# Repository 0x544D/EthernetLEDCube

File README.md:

# EthernetLEDCube
This project contains the PCB design files and software of the Ethernet controlled 6x6x6 LED Cube project. The project was successfully finished within the "System-on-Chip (SOC) + ARM Lab" course of TU Berlin.

Further information about the project can be found in the doc folder.

Project member:
* Tobias Minn
* Arne Salzwedel
* Julian Gog
* Max Thonagel

# Video of the result

# Pictures

Picture of the FPGA Board and the designed LED Cube PCB:

Animation on the Cube:

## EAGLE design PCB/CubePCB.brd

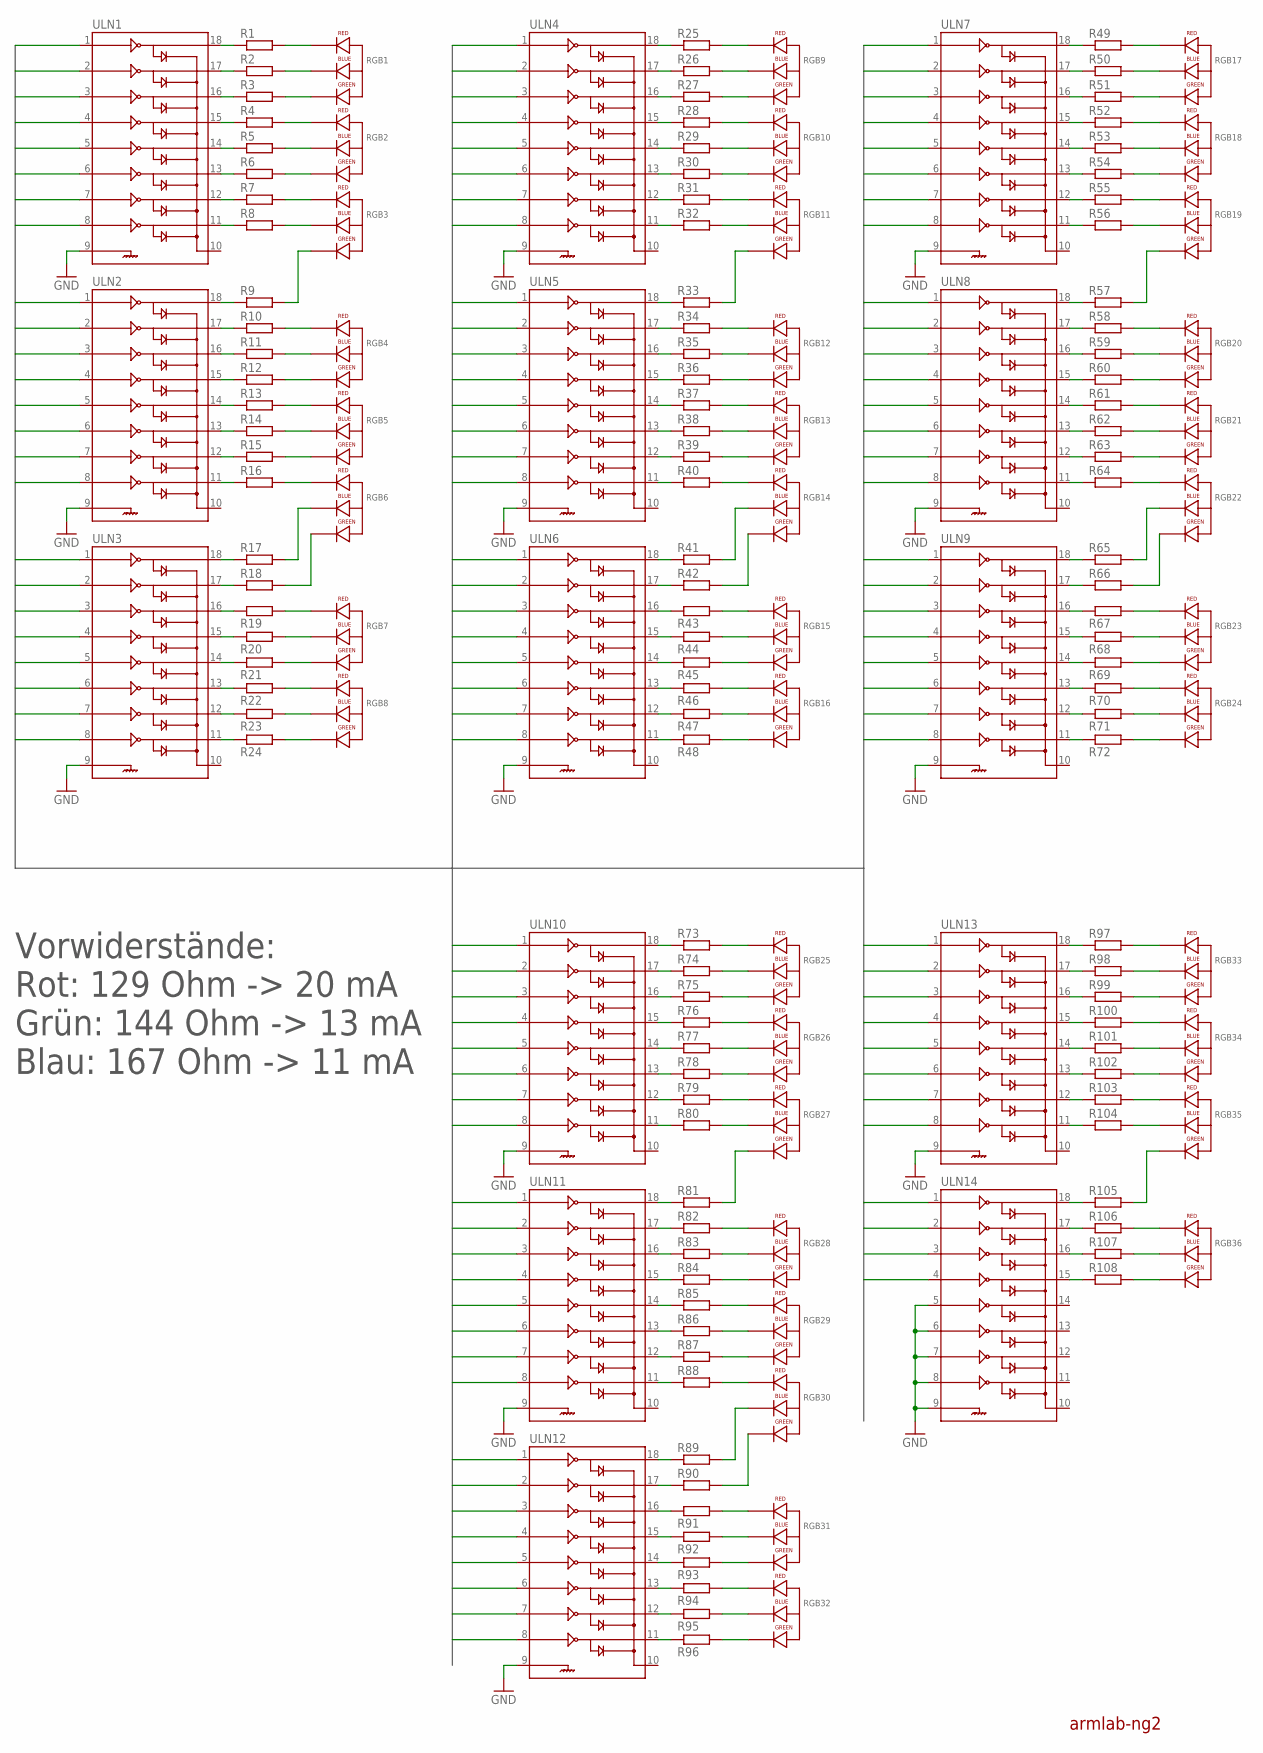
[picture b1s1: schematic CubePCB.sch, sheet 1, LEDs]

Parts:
R1, R2, R3, R4, R5, R6, R7, R8, R9, R10, R11, R12, R13, R14, R15, R16, R17, R18, R19, R20, R21, R22, R23, R24, R25, R26, R27, R28, R29, R30, R31, R32, R33, R34, R35, R36, R37, R38, R39, R40, R41, R42, R43, R44, R45, R46, R47, R48, R49, R50, R51, R52, R53, R54, R55, R56, R57, R58, R59, R60, R61, R62, R63, R64, R65, R66, R67, R68, R69, R70, R71, R72, R73, R74, R75, R76, R77, R78, R79, R80, R81, R82, R83, R84, R85, R86, R87, R88, R89, R90, R91, R92, R93, R94, R95, R96, R97, R98, R99, R100, R101, R102, R103, R104, R105, R106, R107, R108: R-EU_R0603; R0603
RGB1, RGB2, RGB3, RGB4, RGB5, RGB6, RGB7, RGB8, RGB9, RGB10, RGB11, RGB12, RGB13, RGB14, RGB15, RGB16, RGB17, RGB18, RGB19, RGB20, RGB21, RGB22, RGB23, RGB24, RGB25, RGB26, RGB27, RGB28, RGB29, RGB30, RGB31, RGB32, RGB33, RGB34, RGB35, RGB36: LED-RGB-CA-ANODE-SPLIT; LED-RGB-WO-ANODE
ULN1, ULN2, ULN3, ULN4, ULN5, ULN6, ULN7, ULN8, ULN9, ULN10, ULN11, ULN12, ULN13, ULN14: ULN2803SOICW; SO18L

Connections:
B1: ULN1.2; also elsewhere on the board
B2: ULN1.5; also elsewhere on the board
B3: ULN1.8; also elsewhere on the board
B4: ULN2.3; also elsewhere on the board
B5: ULN2.6; also elsewhere on the board
B6: ULN3.1; also elsewhere on the board
B7: ULN3.4; also elsewhere on the board
B8: ULN3.7; also elsewhere on the board
B9: ULN4.2; also elsewhere on the board
B10: ULN4.5; also elsewhere on the board
B11: ULN4.8; also elsewhere on the board
B12: ULN5.3; also elsewhere on the board
B13: ULN5.6; also elsewhere on the board
B14: ULN6.1; also elsewhere on the board
B15: ULN6.4; also elsewhere on the board
B16: ULN6.7; also elsewhere on the board
B17: ULN7.2; also elsewhere on the board
B18: ULN7.5; also elsewhere on the board
B19: ULN7.8; also elsewhere on the board
B20: ULN8.3; also elsewhere on the board
B21: ULN8.6; also elsewhere on the board
B22: ULN9.1; also elsewhere on the board
B23: ULN9.4; also elsewhere on the board
B24: ULN9.7; also elsewhere on the board
B25: ULN10.2; also elsewhere on the board
B26: ULN10.5; also elsewhere on the board
B27: ULN10.8; also elsewhere on the board
B28: ULN11.3; also elsewhere on the board
B29: ULN11.6; also elsewhere on the board
B30: ULN12.1; also elsewhere on the board
B31: ULN12.4; also elsewhere on the board
B32: ULN12.7; also elsewhere on the board
B33: ULN13.2; also elsewhere on the board
B34: ULN13.5; also elsewhere on the board
B35: ULN13.8; also elsewhere on the board
B36: ULN14.3; also elsewhere on the board
G1: ULN1.3; also elsewhere on the board
G2: ULN1.6; also elsewhere on the board
G3: ULN2.1; also elsewhere on the board
G4: ULN2.4; also elsewhere on the board
G5: ULN2.7; also elsewhere on the board
G6: ULN3.2; also elsewhere on the board
G7: ULN3.5; also elsewhere on the board
G8: ULN3.8; also elsewhere on the board
G9: ULN4.3; also elsewhere on the board
G10: ULN4.6; also elsewhere on the board
G11: ULN5.1; also elsewhere on the board
G12: ULN5.4; also elsewhere on the board
G13: ULN5.7; also elsewhere on the board
G14: ULN6.2; also elsewhere on the board
G15: ULN6.5; also elsewhere on the board
G16: ULN6.8; also elsewhere on the board
G17: ULN7.3; also elsewhere on the board
G18: ULN7.6; also elsewhere on the board
G19: ULN8.1; also elsewhere on the board
G20: ULN8.4; also elsewhere on the board
G21: ULN8.7; also elsewhere on the board
G22: ULN9.2; also elsewhere on the board
G23: ULN9.5; also elsewhere on the board
G24: ULN9.8; also elsewhere on the board
G25: ULN10.3; also elsewhere on the board
G26: ULN10.6; also elsewhere on the board
G27: ULN11.1; also elsewhere on the board
G28: ULN11.4; also elsewhere on the board
G29: ULN11.7; also elsewhere on the board
G30: ULN12.2; also elsewhere on the board
G31: ULN12.5; also elsewhere on the board
G32: ULN12.8; also elsewhere on the board
G33: ULN13.3; also elsewhere on the board
G34: ULN13.6; also elsewhere on the board
G35: ULN14.1; also elsewhere on the board
G36: ULN14.4; also elsewhere on the board
GND: ULN1.9, ULN2.9, ULN3.9, ULN4.9, ULN5.9, ULN6.9, ULN7.9, ULN8.9, ULN9.9, ULN10.9, ULN11.9, ULN12.9, ULN13.9, ULN14.5, ULN14.6, ULN14.7, ULN14.8, ULN14.9; also elsewhere on the board
unnamed: R1.1, ULN1.18
unnamed: R2.1, ULN1.17
unnamed: R3.1, ULN1.16
unnamed: R3.2, RGB1.G (GREEN_CATHODE)
unnamed: R2.2, RGB1.B (BLUE_CATHODE)
unnamed: R1.2, RGB1.R (RED_CATHODE)
unnamed: R4.1, ULN1.15
unnamed: R5.1, ULN1.14
unnamed: R6.1, ULN1.13
unnamed: R7.1, ULN1.12
unnamed: R6.2, RGB2.G (GREEN_CATHODE)
unnamed: R5.2, RGB2.B (BLUE_CATHODE)
unnamed: R4.2, RGB2.R (RED_CATHODE)
unnamed: R8.1, ULN1.11
unnamed: R19.1, ULN3.16
unnamed: R20.1, ULN3.15
unnamed: R9.2, RGB3.G (GREEN_CATHODE)
unnamed: R8.2, RGB3.B (BLUE_CATHODE)
unnamed: R7.2, RGB3.R (RED_CATHODE)
unnamed: R21.1, ULN3.14
unnamed: R22.1, ULN3.13
unnamed: R23.1, ULN3.12
unnamed: R12.2, RGB4.G (GREEN_CATHODE)
unnamed: R11.2, RGB4.B (BLUE_CATHODE)
unnamed: R10.2, RGB4.R (RED_CATHODE)
unnamed: R24.1, ULN3.11
unnamed: R27.2, RGB9.G (GREEN_CATHODE)
unnamed: R26.2, RGB9.B (BLUE_CATHODE)
unnamed: R15.2, RGB5.G (GREEN_CATHODE)
unnamed: R14.2, RGB5.B (BLUE_CATHODE)
unnamed: R13.2, RGB5.R (RED_CATHODE)
unnamed: R25.2, RGB9.R (RED_CATHODE)
unnamed: R30.2, RGB10.G (GREEN_CATHODE)
unnamed: R29.2, RGB10.B (BLUE_CATHODE)
unnamed: R18.2, RGB6.G (GREEN_CATHODE)
unnamed: R17.2, RGB6.B (BLUE_CATHODE)
unnamed: R16.2, RGB6.R (RED_CATHODE)
unnamed: R28.2, RGB10.R (RED_CATHODE)
unnamed: R33.2, RGB11.G (GREEN_CATHODE)
unnamed: R32.2, RGB11.B (BLUE_CATHODE)
unnamed: R31.2, RGB11.R (RED_CATHODE)
unnamed: R36.2, RGB12.G (GREEN_CATHODE)
unnamed: R35.2, RGB12.B (BLUE_CATHODE)
unnamed: R34.2, RGB12.R (RED_CATHODE)
unnamed: R19.2, RGB7.R (RED_CATHODE)
unnamed: R20.2, RGB7.B (BLUE_CATHODE)
unnamed: R21.2, RGB7.G (GREEN_CATHODE)
unnamed: R22.2, RGB8.R (RED_CATHODE)
unnamed: R23.2, RGB8.B (BLUE_CATHODE)
unnamed: R24.2, RGB8.G (GREEN_CATHODE)
unnamed: R39.2, RGB13.G (GREEN_CATHODE)
unnamed: R38.2, RGB13.B (BLUE_CATHODE)
unnamed: R9.1, ULN2.18
unnamed: R10.1, ULN2.17
unnamed: R11.1, ULN2.16
unnamed: R12.1, ULN2.15
unnamed: R13.1, ULN2.14
unnamed: R14.1, ULN2.13
unnamed: R15.1, ULN2.12
unnamed: R16.1, ULN2.11
unnamed: R17.1, ULN3.18
unnamed: R18.1, ULN3.17
unnamed: R37.2, RGB13.R (RED_CATHODE)
unnamed: R42.2, RGB14.G (GREEN_CATHODE)
unnamed: R41.2, RGB14.B (BLUE_CATHODE)
unnamed: R40.2, RGB14.R (RED_CATHODE)
unnamed: R25.1, ULN4.18
unnamed: R26.1, ULN4.17
unnamed: R27.1, ULN4.16
unnamed: R28.1, ULN4.15
unnamed: R29.1, ULN4.14
unnamed: R30.1, ULN4.13
unnamed: R31.1, ULN4.12
unnamed: R32.1, ULN4.11
unnamed: R33.1, ULN5.18
unnamed: R34.1, ULN5.17
unnamed: R35.1, ULN5.16
unnamed: R36.1, ULN5.15
unnamed: R37.1, ULN5.14
unnamed: R38.1, ULN5.13
unnamed: R39.1, ULN5.12
unnamed: R40.1, ULN5.11
unnamed: R41.1, ULN6.18
unnamed: R42.1, ULN6.17
unnamed: R43.1, ULN6.16
unnamed: R44.1, ULN6.15
unnamed: R45.1, ULN6.14
unnamed: R46.1, ULN6.13
unnamed: R47.1, ULN6.12
unnamed: R48.1, ULN6.11
unnamed: R43.2, RGB15.R (RED_CATHODE)
unnamed: R44.2, RGB15.B (BLUE_CATHODE)
unnamed: R45.2, RGB15.G (GREEN_CATHODE)
unnamed: R46.2, RGB16.R (RED_CATHODE)
unnamed: R47.2, RGB16.B (BLUE_CATHODE)
unnamed: R48.2, RGB16.G (GREEN_CATHODE)
unnamed: R51.2, RGB17.G (GREEN_CATHODE)
unnamed: R50.2, RGB17.B (BLUE_CATHODE)
unnamed: R49.2, RGB17.R (RED_CATHODE)
unnamed: R54.2, RGB18.G (GREEN_CATHODE)
unnamed: R53.2, RGB18.B (BLUE_CATHODE)
unnamed: R52.2, RGB18.R (RED_CATHODE)
unnamed: R57.2, RGB19.G (GREEN_CATHODE)
unnamed: R56.2, RGB19.B (BLUE_CATHODE)
unnamed: R55.2, RGB19.R (RED_CATHODE)
unnamed: R60.2, RGB20.G (GREEN_CATHODE)
unnamed: R59.2, RGB20.B (BLUE_CATHODE)
unnamed: R58.2, RGB20.R (RED_CATHODE)
unnamed: R63.2, RGB21.G (GREEN_CATHODE)
unnamed: R62.2, RGB21.B (BLUE_CATHODE)
unnamed: R61.2, RGB21.R (RED_CATHODE)
unnamed: R66.2, RGB22.G (GREEN_CATHODE)
unnamed: R65.2, RGB22.B (BLUE_CATHODE)
unnamed: R64.2, RGB22.R (RED_CATHODE)
unnamed: R49.1, ULN7.18
unnamed: R50.1, ULN7.17
unnamed: R51.1, ULN7.16
unnamed: R52.1, ULN7.15
unnamed: R53.1, ULN7.14
unnamed: R54.1, ULN7.13
unnamed: R55.1, ULN7.12
unnamed: R56.1, ULN7.11
unnamed: R57.1, ULN8.18
unnamed: R58.1, ULN8.17
unnamed: R59.1, ULN8.16
unnamed: R60.1, ULN8.15
unnamed: R61.1, ULN8.14
unnamed: R62.1, ULN8.13
unnamed: R63.1, ULN8.12
unnamed: R64.1, ULN8.11
unnamed: R65.1, ULN9.18
unnamed: R66.1, ULN9.17
unnamed: R67.1, ULN9.16
unnamed: R68.1, ULN9.15
unnamed: R69.1, ULN9.14
unnamed: R70.1, ULN9.13
unnamed: R71.1, ULN9.12
unnamed: R72.1, ULN9.11
unnamed: R67.2, RGB23.R (RED_CATHODE)
unnamed: R68.2, RGB23.B (BLUE_CATHODE)
unnamed: R69.2, RGB23.G (GREEN_CATHODE)
unnamed: R70.2, RGB24.R (RED_CATHODE)
unnamed: R71.2, RGB24.B (BLUE_CATHODE)
unnamed: R72.2, RGB24.G (GREEN_CATHODE)
unnamed: R75.2, RGB25.G (GREEN_CATHODE)
unnamed: R74.2, RGB25.B (BLUE_CATHODE)
unnamed: R73.2, RGB25.R (RED_CATHODE)
unnamed: R78.2, RGB26.G (GREEN_CATHODE)
unnamed: R77.2, RGB26.B (BLUE_CATHODE)
unnamed: R76.2, RGB26.R (RED_CATHODE)
unnamed: R81.2, RGB27.G (GREEN_CATHODE)
unnamed: R80.2, RGB27.B (BLUE_CATHODE)
unnamed: R79.2, RGB27.R (RED_CATHODE)
unnamed: R84.2, RGB28.G (GREEN_CATHODE)
unnamed: R83.2, RGB28.B (BLUE_CATHODE)
unnamed: R82.2, RGB28.R (RED_CATHODE)
unnamed: R87.2, RGB29.G (GREEN_CATHODE)
unnamed: R86.2, RGB29.B (BLUE_CATHODE)
unnamed: R85.2, RGB29.R (RED_CATHODE)
unnamed: R90.2, RGB30.G (GREEN_CATHODE)
unnamed: R89.2, RGB30.B (BLUE_CATHODE)
unnamed: R88.2, RGB30.R (RED_CATHODE)
unnamed: R73.1, ULN10.18
unnamed: R74.1, ULN10.17
unnamed: R75.1, ULN10.16
unnamed: R76.1, ULN10.15
unnamed: R77.1, ULN10.14
unnamed: R78.1, ULN10.13
unnamed: R79.1, ULN10.12
unnamed: R80.1, ULN10.11
unnamed: R81.1, ULN11.18
unnamed: R82.1, ULN11.17
unnamed: R83.1, ULN11.16
unnamed: R84.1, ULN11.15
unnamed: R85.1, ULN11.14
unnamed: R86.1, ULN11.13
unnamed: R87.1, ULN11.12
unnamed: R88.1, ULN11.11
unnamed: R89.1, ULN12.18
unnamed: R90.1, ULN12.17
unnamed: R91.1, ULN12.16
unnamed: R92.1, ULN12.15
unnamed: R93.1, ULN12.14
unnamed: R94.1, ULN12.13
unnamed: R95.1, ULN12.12
unnamed: R96.1, ULN12.11
unnamed: R91.2, RGB31.R (RED_CATHODE)
unnamed: R92.2, RGB31.B (BLUE_CATHODE)
unnamed: R93.2, RGB31.G (GREEN_CATHODE)
unnamed: R94.2, RGB32.R (RED_CATHODE)
unnamed: R95.2, RGB32.B (BLUE_CATHODE)
unnamed: R96.2, RGB32.G (GREEN_CATHODE)
unnamed: R99.2, RGB33.G (GREEN_CATHODE)
unnamed: R98.2, RGB33.B (BLUE_CATHODE)
unnamed: R97.2, RGB33.R (RED_CATHODE)
unnamed: R102.2, RGB34.G (GREEN_CATHODE)
unnamed: R101.2, RGB34.B (BLUE_CATHODE)
unnamed: R100.2, RGB34.R (RED_CATHODE)
unnamed: R105.2, RGB35.G (GREEN_CATHODE)
unnamed: R104.2, RGB35.B (BLUE_CATHODE)
unnamed: R103.2, RGB35.R (RED_CATHODE)
unnamed: R108.2, RGB36.G (GREEN_CATHODE)
unnamed: R107.2, RGB36.B (BLUE_CATHODE)
unnamed: R106.2, RGB36.R (RED_CATHODE)
unnamed: R97.1, ULN13.18
unnamed: R98.1, ULN13.17
unnamed: R99.1, ULN13.16
unnamed: R100.1, ULN13.15
unnamed: R101.1, ULN13.14
unnamed: R102.1, ULN13.13
unnamed: R103.1, ULN13.12
unnamed: R104.1, ULN13.11
unnamed: R105.1, ULN14.18
unnamed: R106.1, ULN14.17
unnamed: R107.1, ULN14.16
unnamed: R108.1, ULN14.15
R1: ULN1.1; also elsewhere on the board
R2: ULN1.4; also elsewhere on the board
R3: ULN1.7; also elsewhere on the board
R4: ULN2.2; also elsewhere on the board
R5: ULN2.5; also elsewhere on the board
R6: ULN2.8; also elsewhere on the board
R7: ULN3.3; also elsewhere on the board
R8: ULN3.6; also elsewhere on the board
R9: ULN4.1; also elsewhere on the board
R10: ULN4.4; also elsewhere on the board
R11: ULN4.7; also elsewhere on the board
R12: ULN5.2; also elsewhere on the board
R13: ULN5.5; also elsewhere on the board
R14: ULN5.8; also elsewhere on the board
R15: ULN6.3; also elsewhere on the board
R16: ULN6.6; also elsewhere on the board
R17: ULN7.1; also elsewhere on the board
R18: ULN7.4; also elsewhere on the board
R19: ULN7.7; also elsewhere on the board
R20: ULN8.2; also elsewhere on the board
R21: ULN8.5; also elsewhere on the board
R22: ULN8.8; also elsewhere on the board
R23: ULN9.3; also elsewhere on the board
R24: ULN9.6; also elsewhere on the board
R25: ULN10.1; also elsewhere on the board
R26: ULN10.4; also elsewhere on the board
R27: ULN10.7; also elsewhere on the board
R28: ULN11.2; also elsewhere on the board
R29: ULN11.5; also elsewhere on the board
R30: ULN11.8; also elsewhere on the board
R31: ULN12.3; also elsewhere on the board
R32: ULN12.6; also elsewhere on the board
R33: ULN13.1; also elsewhere on the board
R34: ULN13.4; also elsewhere on the board
R35: ULN13.7; also elsewhere on the board
R36: ULN14.2; also elsewhere on the board

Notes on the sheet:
Vorwiderstände: Rot: 129 Ohm -> 20 mA Grün: 144 Ohm -> 13 mA Blau: 167 Ohm -> 11 mA
armlab-ng2

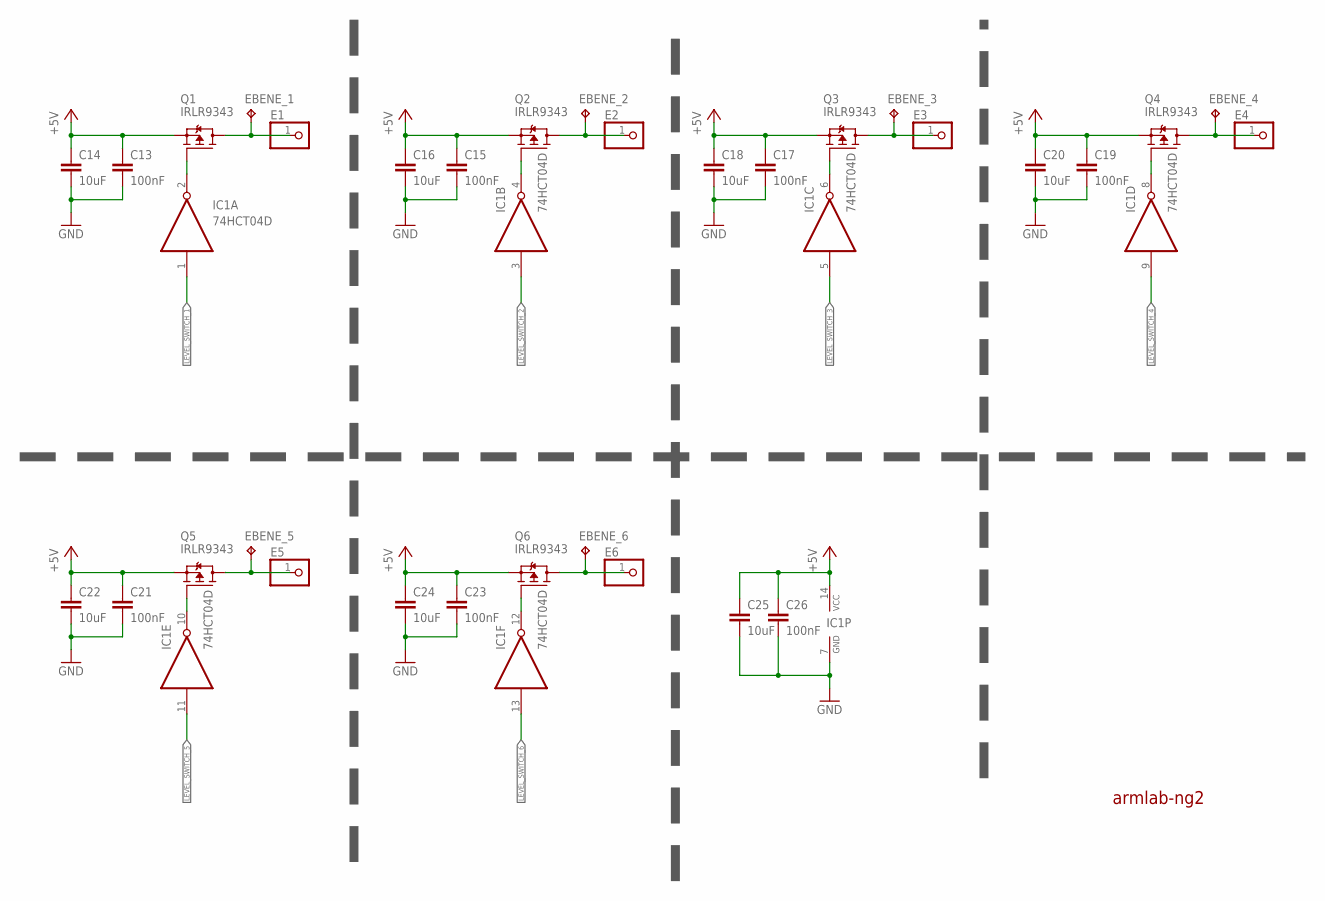
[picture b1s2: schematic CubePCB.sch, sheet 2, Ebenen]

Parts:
C13, C15, C17, C19, C21, C23, C26: 100nF; C0603K
C14, C16, C18, C20, C22, C24, C25: 10uF; C0603K
E1, E2, E3, E4, E5, E6: PINHD-1X1/LONG; 1X01
EBENE_1, EBENE_2, EBENE_3, EBENE_4, EBENE_5, EBENE_6: TPB1,27; B1,27
IC1: 74HCT04D; SO14
Q1, Q2, Q3, Q4, Q5, Q6: IRLR9343; TO252

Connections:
+5V: C13.1, C14.1, C15.1, C16.1, C17.1, C18.1, C19.1, C20.1, C21.1, C22.1, C23.1, C24.1, C25.1, C26.1, IC1.14 (VCC), Q1.2 (S), Q2.2 (S), Q3.2 (S), Q4.2 (S), Q5.2 (S), Q6.2 (S); also elsewhere on the board
EBENE_1: E1.1, EBENE_1.TP, Q1.3 (D)
EBENE_2: E2.1, EBENE_2.TP, Q2.3 (D)
EBENE_3: E3.1, EBENE_3.TP, Q3.3 (D)
EBENE_4: E4.1, EBENE_4.TP, Q4.3 (D)
EBENE_5: E5.1, EBENE_5.TP, Q5.3 (D)
EBENE_6: E6.1, EBENE_6.TP, Q6.3 (D)
GND: C13.2, C14.2, C15.2, C16.2, C17.2, C18.2, C19.2, C20.2, C21.2, C22.2, C23.2, C24.2, C25.2, C26.2, IC1.7 (GND); also elsewhere on the board
LEVEL_SWITCH_1: IC1.1 (I); also elsewhere on the board
LEVEL_SWITCH_2: IC1.3 (I); also elsewhere on the board
LEVEL_SWITCH_3: IC1.5 (I); also elsewhere on the board
LEVEL_SWITCH_4: IC1.9 (I); also elsewhere on the board
LEVEL_SWITCH_5: IC1.11 (I); also elsewhere on the board
LEVEL_SWITCH_6: IC1.13 (I); also elsewhere on the board
unnamed: IC1.4 (O), Q2.1 (G)
unnamed: IC1.2 (O), Q1.1 (G)
unnamed: IC1.6 (O), Q3.1 (G)
unnamed: IC1.8 (O), Q4.1 (G)
unnamed: IC1.10 (O), Q5.1 (G)
unnamed: IC1.12 (O), Q6.1 (G)

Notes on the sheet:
armlab-ng2

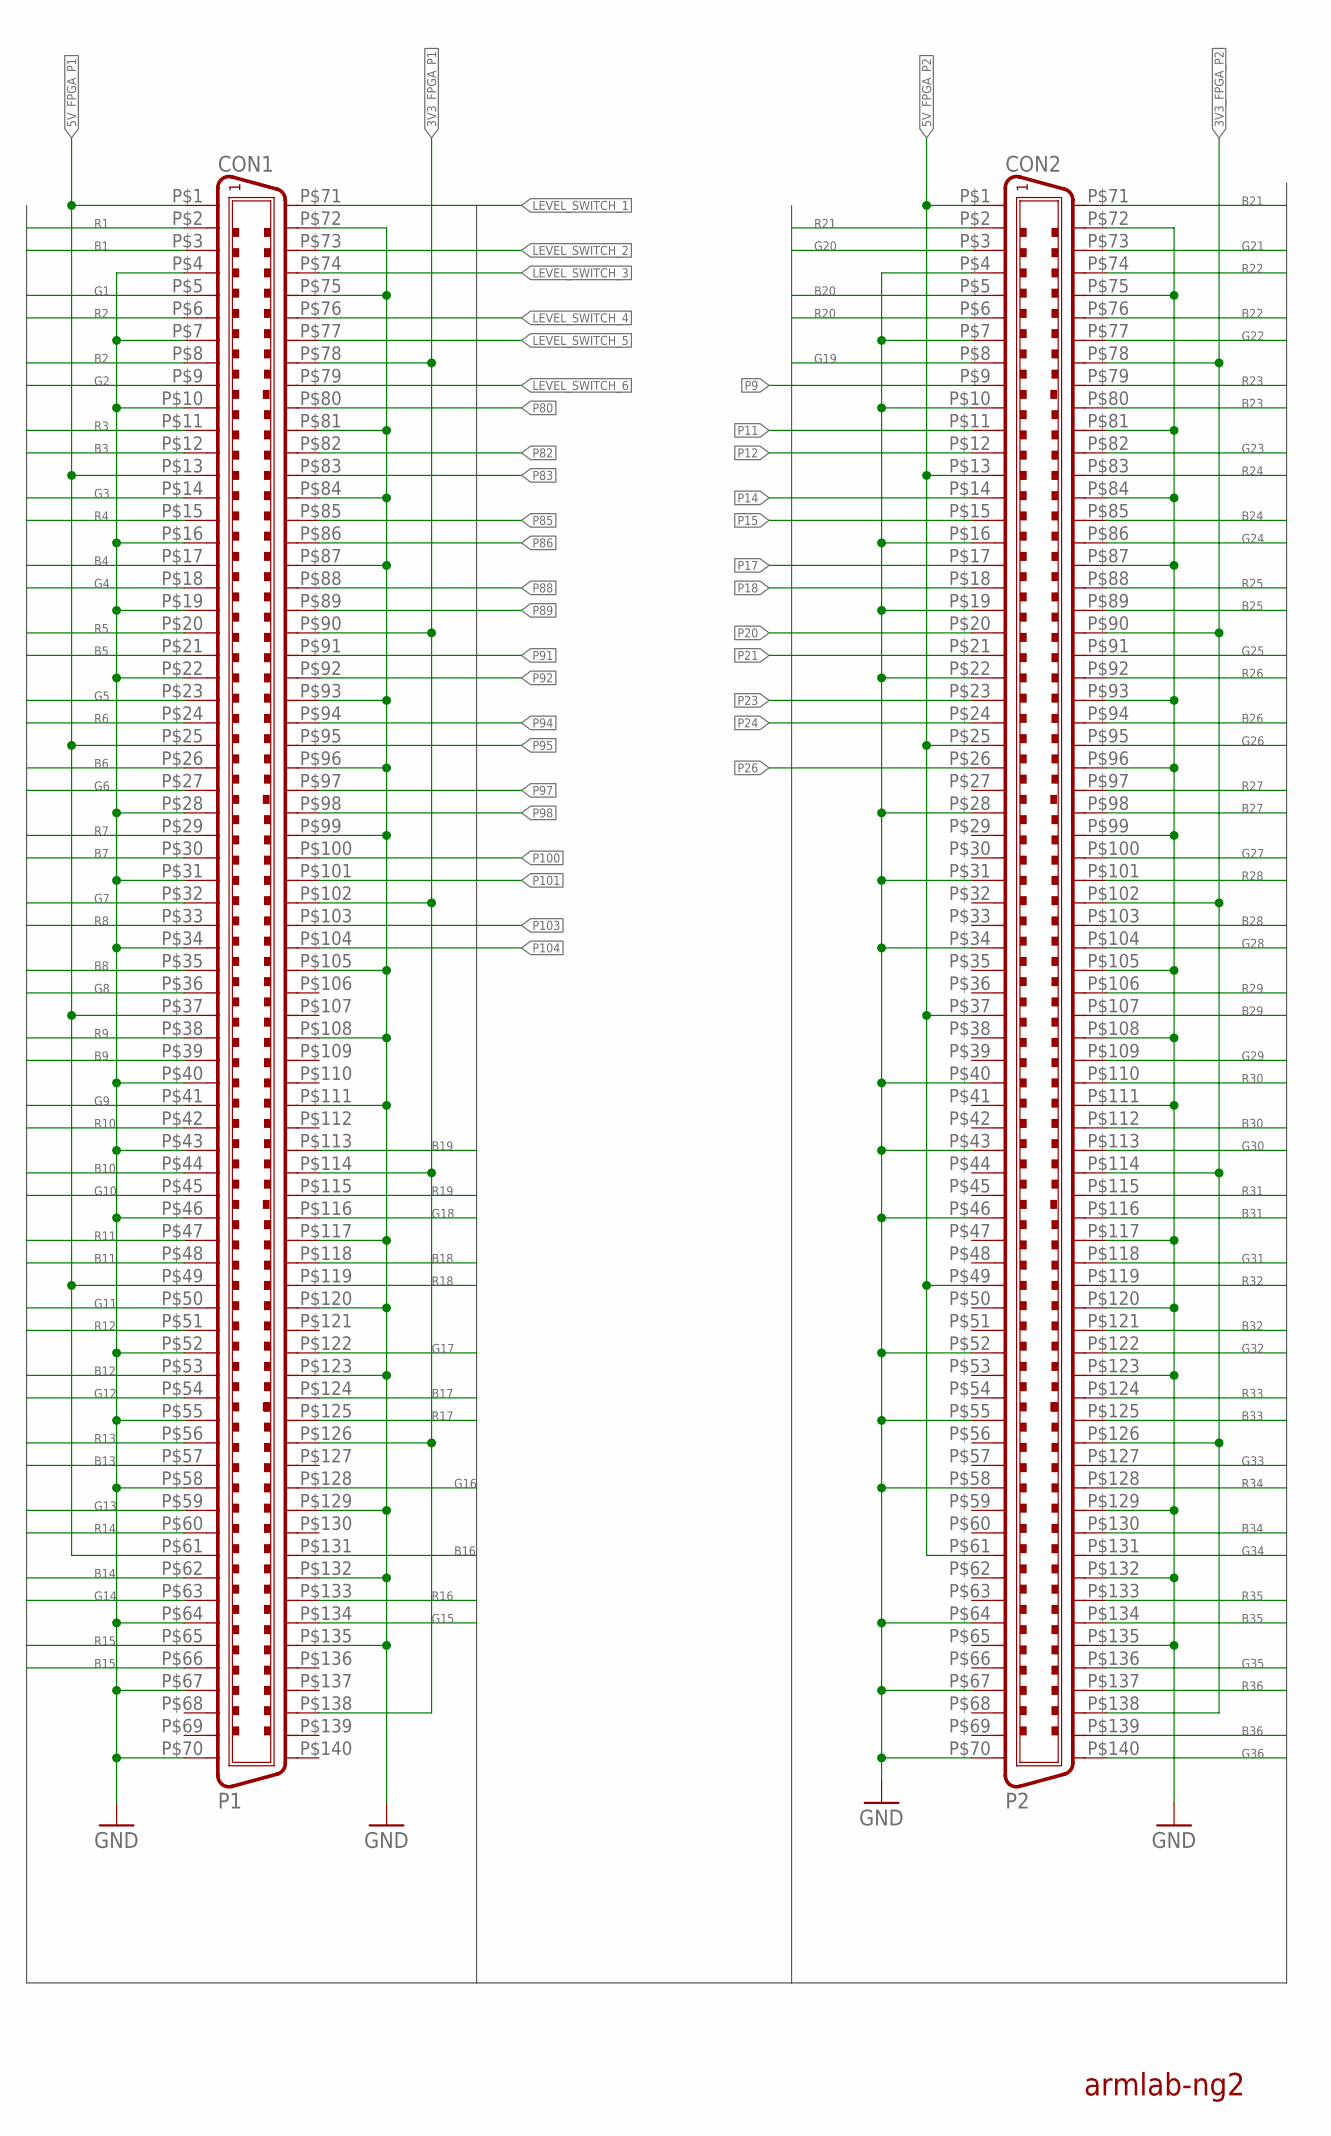
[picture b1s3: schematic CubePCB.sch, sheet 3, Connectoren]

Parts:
CON1: P1; 140-FH0.8
CON2: P2; 140-FH0.8

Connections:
3V3_FPGA_P1: CON1.P$78 (78), CON1.P$90 (90), CON1.P$102 (102), CON1.P$114 (114), CON1.P$126 (126), CON1.P$138 (138)
3V3_FPGA_P2: CON2.P$78 (78), CON2.P$90 (90), CON2.P$102 (102), CON2.P$114 (114), CON2.P$126 (126), CON2.P$138 (138)
5V_FPGA_P1: CON1.P$1 (1), CON1.P$13 (13), CON1.P$25 (25), CON1.P$37 (37), CON1.P$49 (49), CON1.P$61 (61)
5V_FPGA_P2: CON2.P$1 (1), CON2.P$13 (13), CON2.P$25 (25), CON2.P$37 (37), CON2.P$49 (49), CON2.P$61 (61)
B1: CON1.P$3 (3); also elsewhere on the board
B2: CON1.P$8 (8); also elsewhere on the board
B3: CON1.P$12 (12); also elsewhere on the board
B4: CON1.P$17 (17); also elsewhere on the board
B5: CON1.P$21 (21); also elsewhere on the board
B6: CON1.P$26 (26); also elsewhere on the board
B7: CON1.P$30 (30); also elsewhere on the board
B8: CON1.P$35 (35); also elsewhere on the board
B9: CON1.P$39 (39); also elsewhere on the board
B10: CON1.P$44 (44); also elsewhere on the board
B11: CON1.P$48 (48); also elsewhere on the board
B12: CON1.P$53 (53); also elsewhere on the board
B13: CON1.P$57 (57); also elsewhere on the board
B14: CON1.P$62 (62); also elsewhere on the board
B15: CON1.P$66 (66); also elsewhere on the board
B16: CON1.P$131 (131); also elsewhere on the board
B17: CON1.P$124 (124); also elsewhere on the board
B18: CON1.P$118 (118); also elsewhere on the board
B19: CON1.P$113 (113); also elsewhere on the board
B20: CON2.P$5 (5); also elsewhere on the board
B21: CON2.P$71 (71); also elsewhere on the board
B22: CON2.P$76 (76); also elsewhere on the board
B23: CON2.P$80 (80); also elsewhere on the board
B24: CON2.P$85 (85); also elsewhere on the board
B25: CON2.P$89 (89); also elsewhere on the board
B26: CON2.P$94 (94); also elsewhere on the board
B27: CON2.P$98 (98); also elsewhere on the board
B28: CON2.P$103 (103); also elsewhere on the board
B29: CON2.P$107 (107); also elsewhere on the board
B30: CON2.P$112 (112); also elsewhere on the board
B31: CON2.P$116 (116); also elsewhere on the board
B32: CON2.P$121 (121); also elsewhere on the board
B33: CON2.P$125 (125); also elsewhere on the board
B34: CON2.P$130 (130); also elsewhere on the board
B35: CON2.P$134 (134); also elsewhere on the board
B36: CON2.P$139 (139); also elsewhere on the board
G1: CON1.P$5 (5); also elsewhere on the board
G2: CON1.P$9 (9); also elsewhere on the board
G3: CON1.P$14 (14); also elsewhere on the board
G4: CON1.P$18 (18); also elsewhere on the board
G5: CON1.P$23 (23); also elsewhere on the board
G6: CON1.P$27 (27); also elsewhere on the board
G7: CON1.P$32 (32); also elsewhere on the board
G8: CON1.P$36 (36); also elsewhere on the board
G9: CON1.P$41 (41); also elsewhere on the board
G10: CON1.P$45 (45); also elsewhere on the board
G11: CON1.P$50 (50); also elsewhere on the board
G12: CON1.P$54 (54); also elsewhere on the board
G13: CON1.P$59 (59); also elsewhere on the board
G14: CON1.P$63 (63); also elsewhere on the board
G15: CON1.P$134 (134); also elsewhere on the board
G16: CON1.P$128 (128); also elsewhere on the board
G17: CON1.P$122 (122); also elsewhere on the board
G18: CON1.P$116 (116); also elsewhere on the board
G19: CON2.P$8 (8); also elsewhere on the board
G20: CON2.P$3 (3); also elsewhere on the board
G21: CON2.P$73 (73); also elsewhere on the board
G22: CON2.P$77 (77); also elsewhere on the board
G23: CON2.P$82 (82); also elsewhere on the board
G24: CON2.P$86 (86); also elsewhere on the board
G25: CON2.P$91 (91); also elsewhere on the board
G26: CON2.P$95 (95); also elsewhere on the board
G27: CON2.P$100 (100); also elsewhere on the board
G28: CON2.P$104 (104); also elsewhere on the board
G29: CON2.P$109 (109); also elsewhere on the board
G30: CON2.P$113 (113); also elsewhere on the board
G31: CON2.P$118 (118); also elsewhere on the board
G32: CON2.P$122 (122); also elsewhere on the board
G33: CON2.P$127 (127); also elsewhere on the board
G34: CON2.P$131 (131); also elsewhere on the board
G35: CON2.P$136 (136); also elsewhere on the board
G36: CON2.P$140 (140); also elsewhere on the board
GND: CON1.P$4 (4), CON1.P$7 (7), CON1.P$10 (10), CON1.P$16 (16), CON1.P$19 (19), CON1.P$22 (22), CON1.P$28 (28), CON1.P$31 (31), CON1.P$34 (34), CON1.P$40 (40), CON1.P$43 (43), CON1.P$46 (46), CON1.P$52 (52), CON1.P$55 (55), CON1.P$58 (58), CON1.P$64 (64), CON1.P$67 (67), CON1.P$70 (70), CON1.P$72 (72), CON1.P$75 (75), CON1.P$81 (81), CON1.P$84 (84), CON1.P$87 (87), CON1.P$93 (93), CON1.P$96 (96), CON1.P$99 (99), CON1.P$105 (105), CON1.P$108 (108), CON1.P$111 (111), CON1.P$117 (117), CON1.P$120 (120), CON1.P$123 (123), CON1.P$129 (129), CON1.P$132 (132), CON1.P$135 (135), CON2.P$4 (4), CON2.P$7 (7), CON2.P$10 (10), CON2.P$16 (16), CON2.P$19 (19), CON2.P$22 (22), CON2.P$28 (28), CON2.P$31 (31), CON2.P$34 (34), CON2.P$40 (40), CON2.P$43 (43), CON2.P$46 (46), CON2.P$52 (52), CON2.P$55 (55), CON2.P$58 (58), CON2.P$64 (64), CON2.P$67 (67), CON2.P$70 (70), CON2.P$72 (72), CON2.P$75 (75), CON2.P$81 (81), CON2.P$84 (84), CON2.P$87 (87), CON2.P$93 (93), CON2.P$96 (96), CON2.P$99 (99), CON2.P$105 (105), CON2.P$108 (108), CON2.P$111 (111), CON2.P$117 (117), CON2.P$120 (120), CON2.P$123 (123), CON2.P$129 (129), CON2.P$132 (132), CON2.P$135 (135); also elsewhere on the board
LEVEL_SWITCH_1: CON1.P$71 (71); also elsewhere on the board
LEVEL_SWITCH_2: CON1.P$73 (73); also elsewhere on the board
LEVEL_SWITCH_3: CON1.P$74 (74); also elsewhere on the board
LEVEL_SWITCH_4: CON1.P$76 (76); also elsewhere on the board
LEVEL_SWITCH_5: CON1.P$77 (77); also elsewhere on the board
LEVEL_SWITCH_6: CON1.P$79 (79); also elsewhere on the board
P9: CON2.P$9 (9)
P11: CON2.P$11 (11)
P12: CON2.P$12 (12)
P14: CON2.P$14 (14)
P15: CON2.P$15 (15)
P17: CON2.P$17 (17)
P18: CON2.P$18 (18)
P20: CON2.P$20 (20)
P21: CON2.P$21 (21)
P23: CON2.P$23 (23)
P24: CON2.P$24 (24)
P26: CON2.P$26 (26)
P80: CON1.P$80 (80)
P82: CON1.P$82 (82)
P83: CON1.P$83 (83)
P85: CON1.P$85 (85)
P86: CON1.P$86 (86)
P88: CON1.P$88 (88)
P89: CON1.P$89 (89)
P91: CON1.P$91 (91)
P92: CON1.P$92 (92)
P94: CON1.P$94 (94)
P95: CON1.P$95 (95)
P97: CON1.P$97 (97)
P98: CON1.P$98 (98)
P100: CON1.P$100 (100)
P101: CON1.P$101 (101)
P103: CON1.P$103 (103)
P104: CON1.P$104 (104)
R1: CON1.P$2 (2); also elsewhere on the board
R2: CON1.P$6 (6); also elsewhere on the board
R3: CON1.P$11 (11); also elsewhere on the board
R4: CON1.P$15 (15); also elsewhere on the board
R5: CON1.P$20 (20); also elsewhere on the board
R6: CON1.P$24 (24); also elsewhere on the board
R7: CON1.P$29 (29); also elsewhere on the board
R8: CON1.P$33 (33); also elsewhere on the board
R9: CON1.P$38 (38); also elsewhere on the board
R10: CON1.P$42 (42); also elsewhere on the board
R11: CON1.P$47 (47); also elsewhere on the board
R12: CON1.P$51 (51); also elsewhere on the board
R13: CON1.P$56 (56); also elsewhere on the board
R14: CON1.P$60 (60); also elsewhere on the board
R15: CON1.P$65 (65); also elsewhere on the board
R16: CON1.P$133 (133); also elsewhere on the board
R17: CON1.P$125 (125); also elsewhere on the board
R18: CON1.P$119 (119); also elsewhere on the board
R19: CON1.P$115 (115); also elsewhere on the board
R20: CON2.P$6 (6); also elsewhere on the board
R21: CON2.P$2 (2); also elsewhere on the board
R22: CON2.P$74 (74); also elsewhere on the board
R23: CON2.P$79 (79); also elsewhere on the board
R24: CON2.P$83 (83); also elsewhere on the board
R25: CON2.P$88 (88); also elsewhere on the board
R26: CON2.P$92 (92); also elsewhere on the board
R27: CON2.P$97 (97); also elsewhere on the board
R28: CON2.P$101 (101); also elsewhere on the board
R29: CON2.P$106 (106); also elsewhere on the board
R30: CON2.P$110 (110); also elsewhere on the board
R31: CON2.P$115 (115); also elsewhere on the board
R32: CON2.P$119 (119); also elsewhere on the board
R33: CON2.P$124 (124); also elsewhere on the board
R34: CON2.P$128 (128); also elsewhere on the board
R35: CON2.P$133 (133); also elsewhere on the board
R36: CON2.P$137 (137); also elsewhere on the board

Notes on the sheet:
armlab-ng2

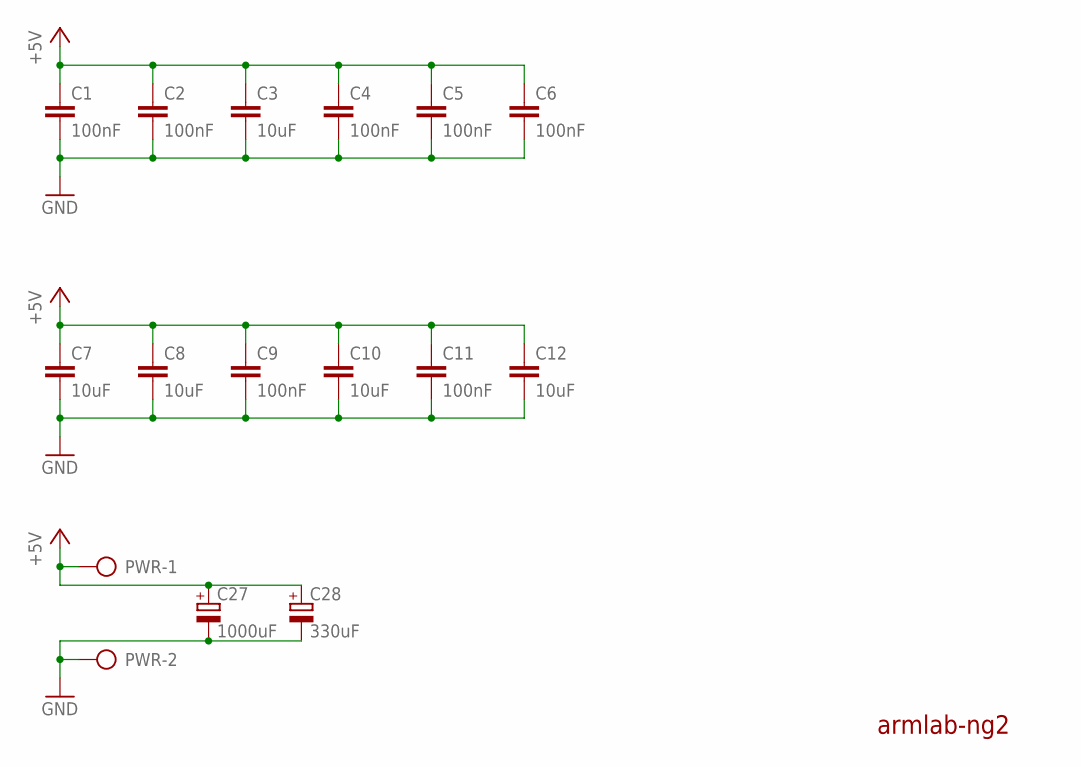
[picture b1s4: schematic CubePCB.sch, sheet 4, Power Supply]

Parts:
C1, C2, C4, C5, C6, C9, C11: 100nF; C0603K
C3, C7, C8, C10, C12: 10uF; C0603K
C27: 1000uF; E5-10,5
C28: 330uF; E3,5-8
PWR: AK500/2

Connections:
+5V: C1.1, C2.1, C3.1, C4.1, C5.1, C6.1, C7.1, C8.1, C9.1, C10.1, C11.1, C12.1, C27.+, C28.+, PWR.1; also elsewhere on the board
GND: C1.2, C2.2, C3.2, C4.2, C5.2, C6.2, C7.2, C8.2, C9.2, C10.2, C11.2, C12.2, C27.-, C28.-, PWR.2; also elsewhere on the board

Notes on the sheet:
armlab-ng2

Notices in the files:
parts and their libraries:
SparkFun-PowerIC: Licensing: Creative Commons ShareAlike 4.0 International - https://creativecommons.org/licenses/by-sa/4.0
